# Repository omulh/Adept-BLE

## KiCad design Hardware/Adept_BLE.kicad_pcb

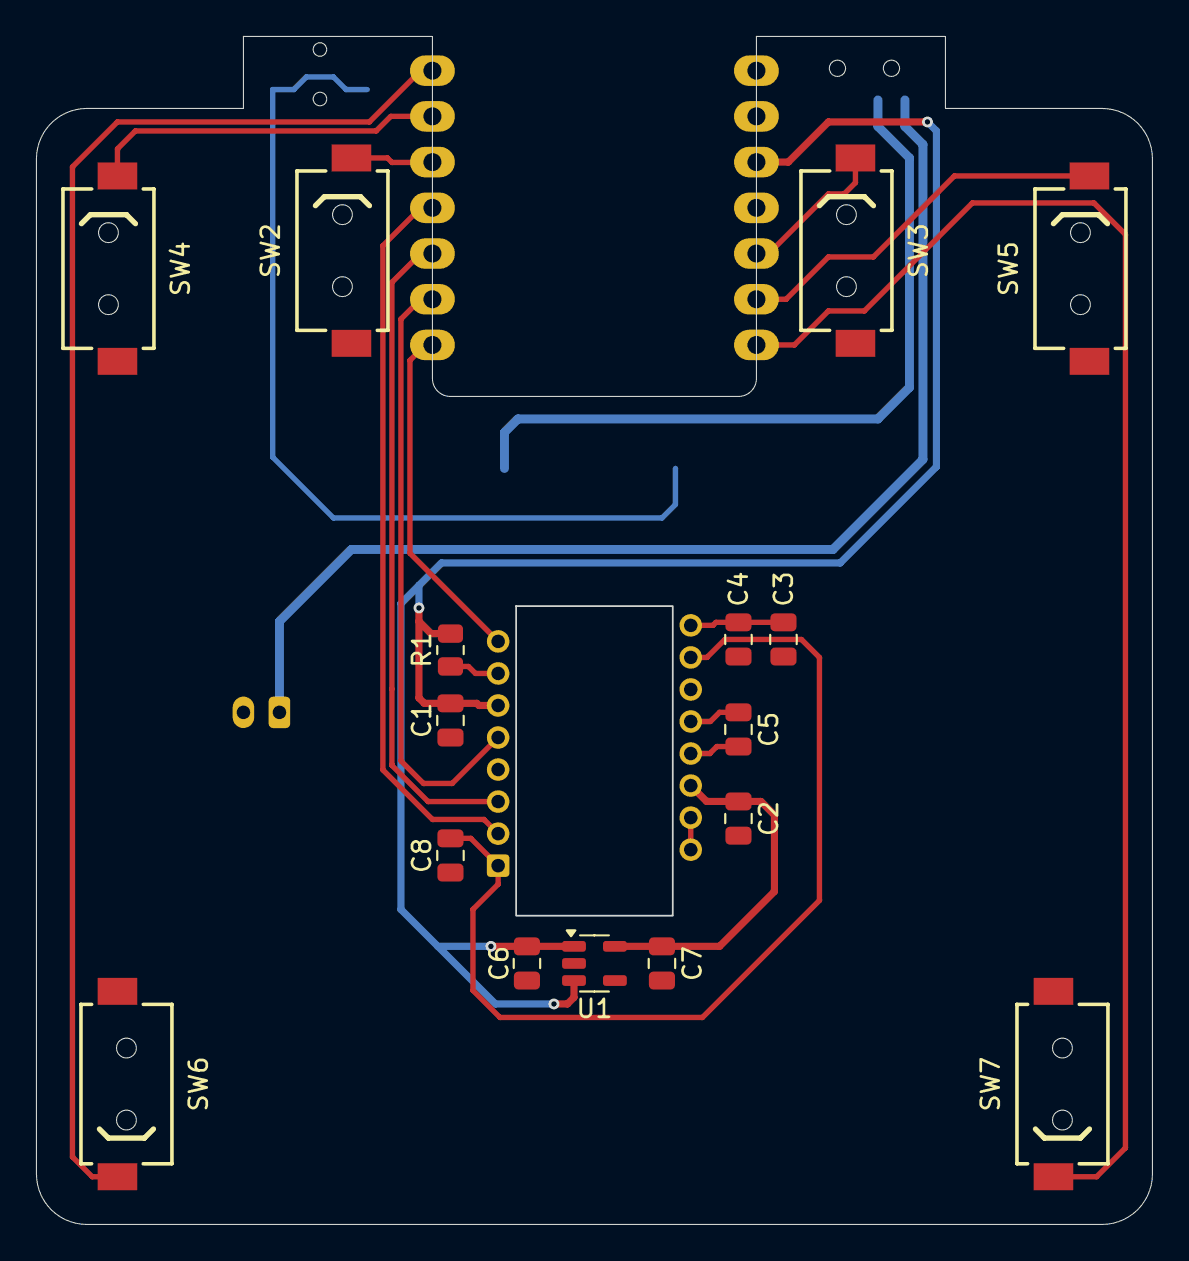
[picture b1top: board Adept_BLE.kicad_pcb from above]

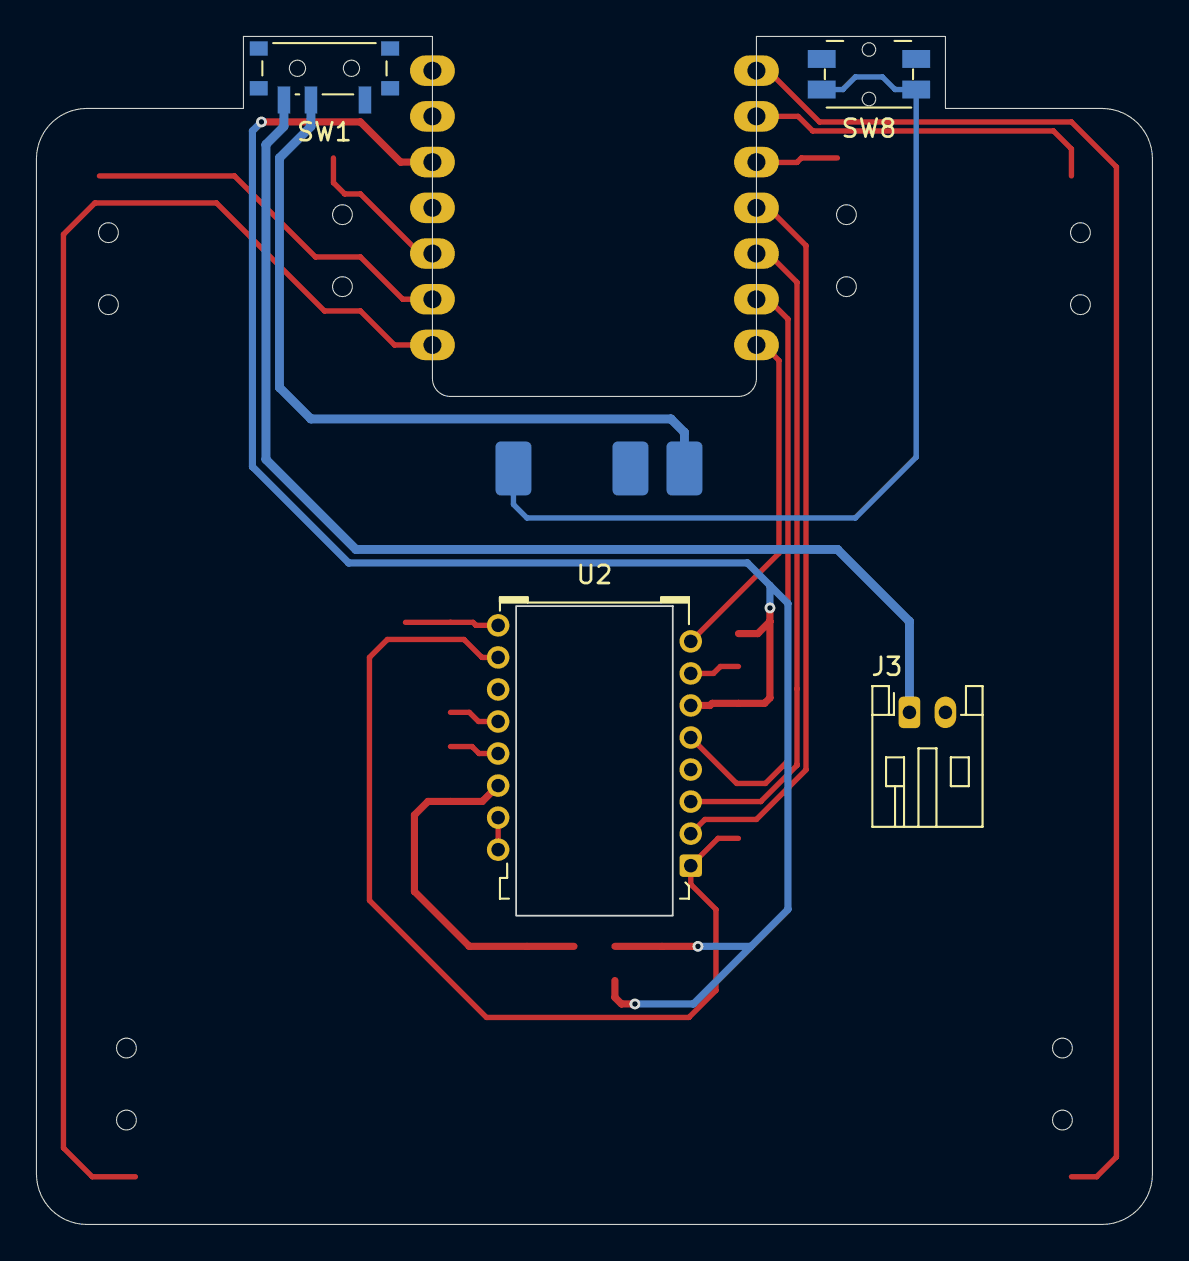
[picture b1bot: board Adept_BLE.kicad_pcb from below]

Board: 2 copper layers, 62.0 x 66.0 mm, 26 parts (7 on the bottom side), 22 nets.

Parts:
C1, C2: 100n; C_0805
C3: 10u/X7R; C_0805
C4: 10n/X7R; C_0805
C5: 100n/X7R; C_0805
C6: 1u; C_0805
C7: 1u/X7R; C_0805
C8: 10n; C_0805
J1, J2, J6: Conn_01x01_Pad; Pad_3x2mm
J3: Conn_01x02_Pin; S2B-PH-K
J4, J5: Conn_01x07_Pad; Through_hole_1x07_P2.54mm
R1: 10k; R_0805
SW1: PCM12SMTR
SW2, SW3, SW4, SW5, SW6, SW7: D2LS-21; D2SL
SW8: EVQPUC02K; EVQPUC
U1: TLV74318P; SOT-23-5
U2: PMW3610DM-SUDU
U3: XIAO-nRF52840-SMD; XIAO_nRF52840_outline

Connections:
+1V8: C2.1, C7.1, U1.5 (OUT), U2.14 (VDD)
+3V3: C1.1, C6.1, J5.3, R1.1, U1.1 (IN), U1.3 (EN), U2.6 (VDDIO)
+BATT: J3.1, SW1.3
+BATT_SW: J2.1, SW1.2
GND: C1.2, C2.2, C3.2, C4.2, C6.2, C7.2, C8.2, J1.1, J3.2, J5.2, SW2.2 (B), SW3.2 (B), SW4.2 (B), SW5.2 (B), SW6.2 (B), SW7.2 (B), SW8.2, SW8.4, U1.2 (GND), U2.11 (GND)
unnamed: C8.1, U2.1 (+VCSEL), U2.10 (PASS_T)
unnamed: U2.15 (XYLASER), U2.16 (-VCSEL)
unnamed: C5.2, U2.13 (CN)
unnamed: C5.1, U2.12 (CP)
unnamed: R1.2, U2.7 (NRESET)
unnamed: C3.1, C4.1, U2.9 (VCP)
PMW_MOTION: J4.7, U2.8 (MOTION)
PMW_NCS: J4.6, U2.5 (NCS)
PMW_SCLK: J4.5, U2.3 (SCLK)
PMW_SDIO: J4.4, U2.2 (SDIO)
SW_LB: J4.1, SW6.1 (A)
SW_LT: J4.2, SW4.1 (A)
SW_ML: J4.3, SW2.1 (A)
SW_MR: J5.5, SW3.1 (A)
SW_RB: J5.7, SW7.1 (A)
SW_RT: J5.6, SW5.1 (A)
XIAO_RST: J6.1, SW8.1, SW8.3

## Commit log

2026-03-01 add README.md
2026-03-01 add .gitignore
2026-03-01 add the Hardware dir., containing the KiCad project
2026-03-02 update the schematics
2026-03-02 update the pcb
2026-03-02 update the project file
2026-03-02 update .gitignore: add .lck files
2026-03-02 update symbol pin names and update schematic accordingly
2026-03-02 update 3d model property of two footprints
2026-03-03 update some text properties of three footprints
2026-03-04 Adept_BLE.kicad_pcb: add layer stack
2026-03-04 Adept_BLE_symbols.kicad_sym: update pin properties in PMW3610 symbol
2026-03-04 add power flags to the schematics
2026-03-04 Adept_BLE.kicad_pro: add constraints and rules
2026-03-04 nrf52840.kicad_sch: update name of global label
2026-03-04 Adept_BLE.kicad_pro: add net classes and their defaults
2026-03-06 Adept_BLE.kicad_pro: update the classes' defaults
2026-04-08 update files for KiCad version 10
2026-04-08 nrf52840.kicad_sch: update the connections of the (not real) U3 symbol
2026-04-08 add Adept_BLE.kicad_dru
2026-04-08 Adept_BLE.kicad_pro: add DRC exclusions
2026-04-08 Adept_BLE.kicad_pcb: update the silkscreen labels
